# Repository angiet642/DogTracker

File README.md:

# DogTracker
__Authors: Kylee and Angie__

### Purpose 

A common issue pet-owners face is discovering that their pet has escaped the house. To prevent this situation, our team is interested in designing a low-power dog tracker using LoRa. Unlike other pet-tracking collars, our system will implement a training technique by emitting a 25KHz sound wave if the pet is found outside of a user-defined geo fence. For example, if the user would like to train their dog to avoid a specific area of the backyard, our device will detect whether the dog is in this region and emit the high frequency sound if so.

### System diagram   
The proposed design of the pet-tracker system is illustrated in the block diagram below.
<p>
  
  <p> Figure 1: System Level Block Diagram
</p>

### Proposed schedule
| Week  | Date | Tasks 
| ------------- | ------------- | ------------- |
| Week 7 | Feb 13-Feb 19  | - [x] Order parts <br />- [ ] Review PCB and Schematic with Steve and Joanna   |
| Week 8 | Feb 20-Feb 26  | - [x] Submit PCB for fabriciation | 
| Week 9 | Feb 27-March 5  | - [ ] Bring up and test boards | 
| Week 10 | March 6-March 12  | - [ ] Demo | 

### Verification
To verify our system, we will first verify the functionality of each module before methodically combining things into our final system. The steps are outlined below.

#### Before final PCB comes back: 
- [x] Upload basic Blink code to M4 Feather Board
- [x] Write basic transmit/recieve code for SX1280 using this [reference](https://github.com/maholli/CircuitPython_SX1280) (In progress)
- [ ] Hook up SX1280 to SPI port of any available micro and run transmit code while probing antenna line with Spectrum Analyzer
- [ ] Connect additional SX1280 board and have both transmit and recieve data \
#### After final PCB comes back:
- [ ] Again, verify transmit and recieve of SX1280 module on our PCB
- [ ] Connect SX1280 to ESP32 (the "base station") and try sending and recieving from our PCB
- [ ] Connect ESP32 to wifi and verify that there isn't any interference between Lora and WIFI
- [ ] Independently turn on GPS and test reading cordinates
- [ ] Turn on both SX1280 and GPS and run code to intermittently send GPS coordinates to "base station" 
- [ ] Configure pedometer to read step count on the microcontroller
- [ ] Read pedometer at the same time as reading GPS and sending Lora
- [ ] Confgure Ultrasonic piezo buzzer and try running at 25kHz, certain apps will verify sound since it's beyond the human range
- [ ] Upload code for runnng piezzo buzzer from the "base station" when dog is out of range
- [ ] Run all four modules at the same time 
- [ ] Have "base station"  upload information to a website hosted on the the Things network

### Demo Plan
Our demo will be putting the collar on a fellow classmate and having them run around the engineering quad to show the real time updates in GPS coordinates on the base station, which will be set up in the lab. Finally, we will show that when our classmate goes out of the user-defined range, the piezzo buzzer will turn on which can be verified with [this app](https://play.google.com/store/apps/details?id=com.microcadsystems.serge.ultrasounddetector&hl=en_US&gl=US)

### In our write up, we will discuss the following
- importance and novelty of the idea 
- description of chosen features 
- high level system discussion
- schematic walkthrough 
- examination of different protocols SPI/I2C/UART 
- Review of RF components eg LoRa, WiFi 
- analysis of challenges or drawbacks
- improvements going forward 
- concluding remarks on our project 

### Challenges
The most difficult steps is getting the PCB right the first time around. We have been meticulously researching parts and going through datasheets to make sure we understand everything that we need for our final PCB. We also plan to have Joanna, Greig, and Steve verify the schematic before we submit it to JLCPCB. 

We have already gotten our parts list checked off and ordered. After submitting our final PCB, we will begin working on the software side of our project. There is a sufficient amount of code to write but none will be outside of our domain given that there's a lot of GPS/LORA/SPI/I2C libraries in Circuit python. 

### Project Links:
Bill of Materials can be found [here](https://github.com/krsandwich/DogTracker/tree/master/Hardware/BOM) \
KICAD Project can be found [here](https://github.com/krsandwich/DogTracker/tree/master/Hardware/Kicad)\
M4 Feather Express Schematic can be found [here](https://learn.adafruit.com/assets/57242)

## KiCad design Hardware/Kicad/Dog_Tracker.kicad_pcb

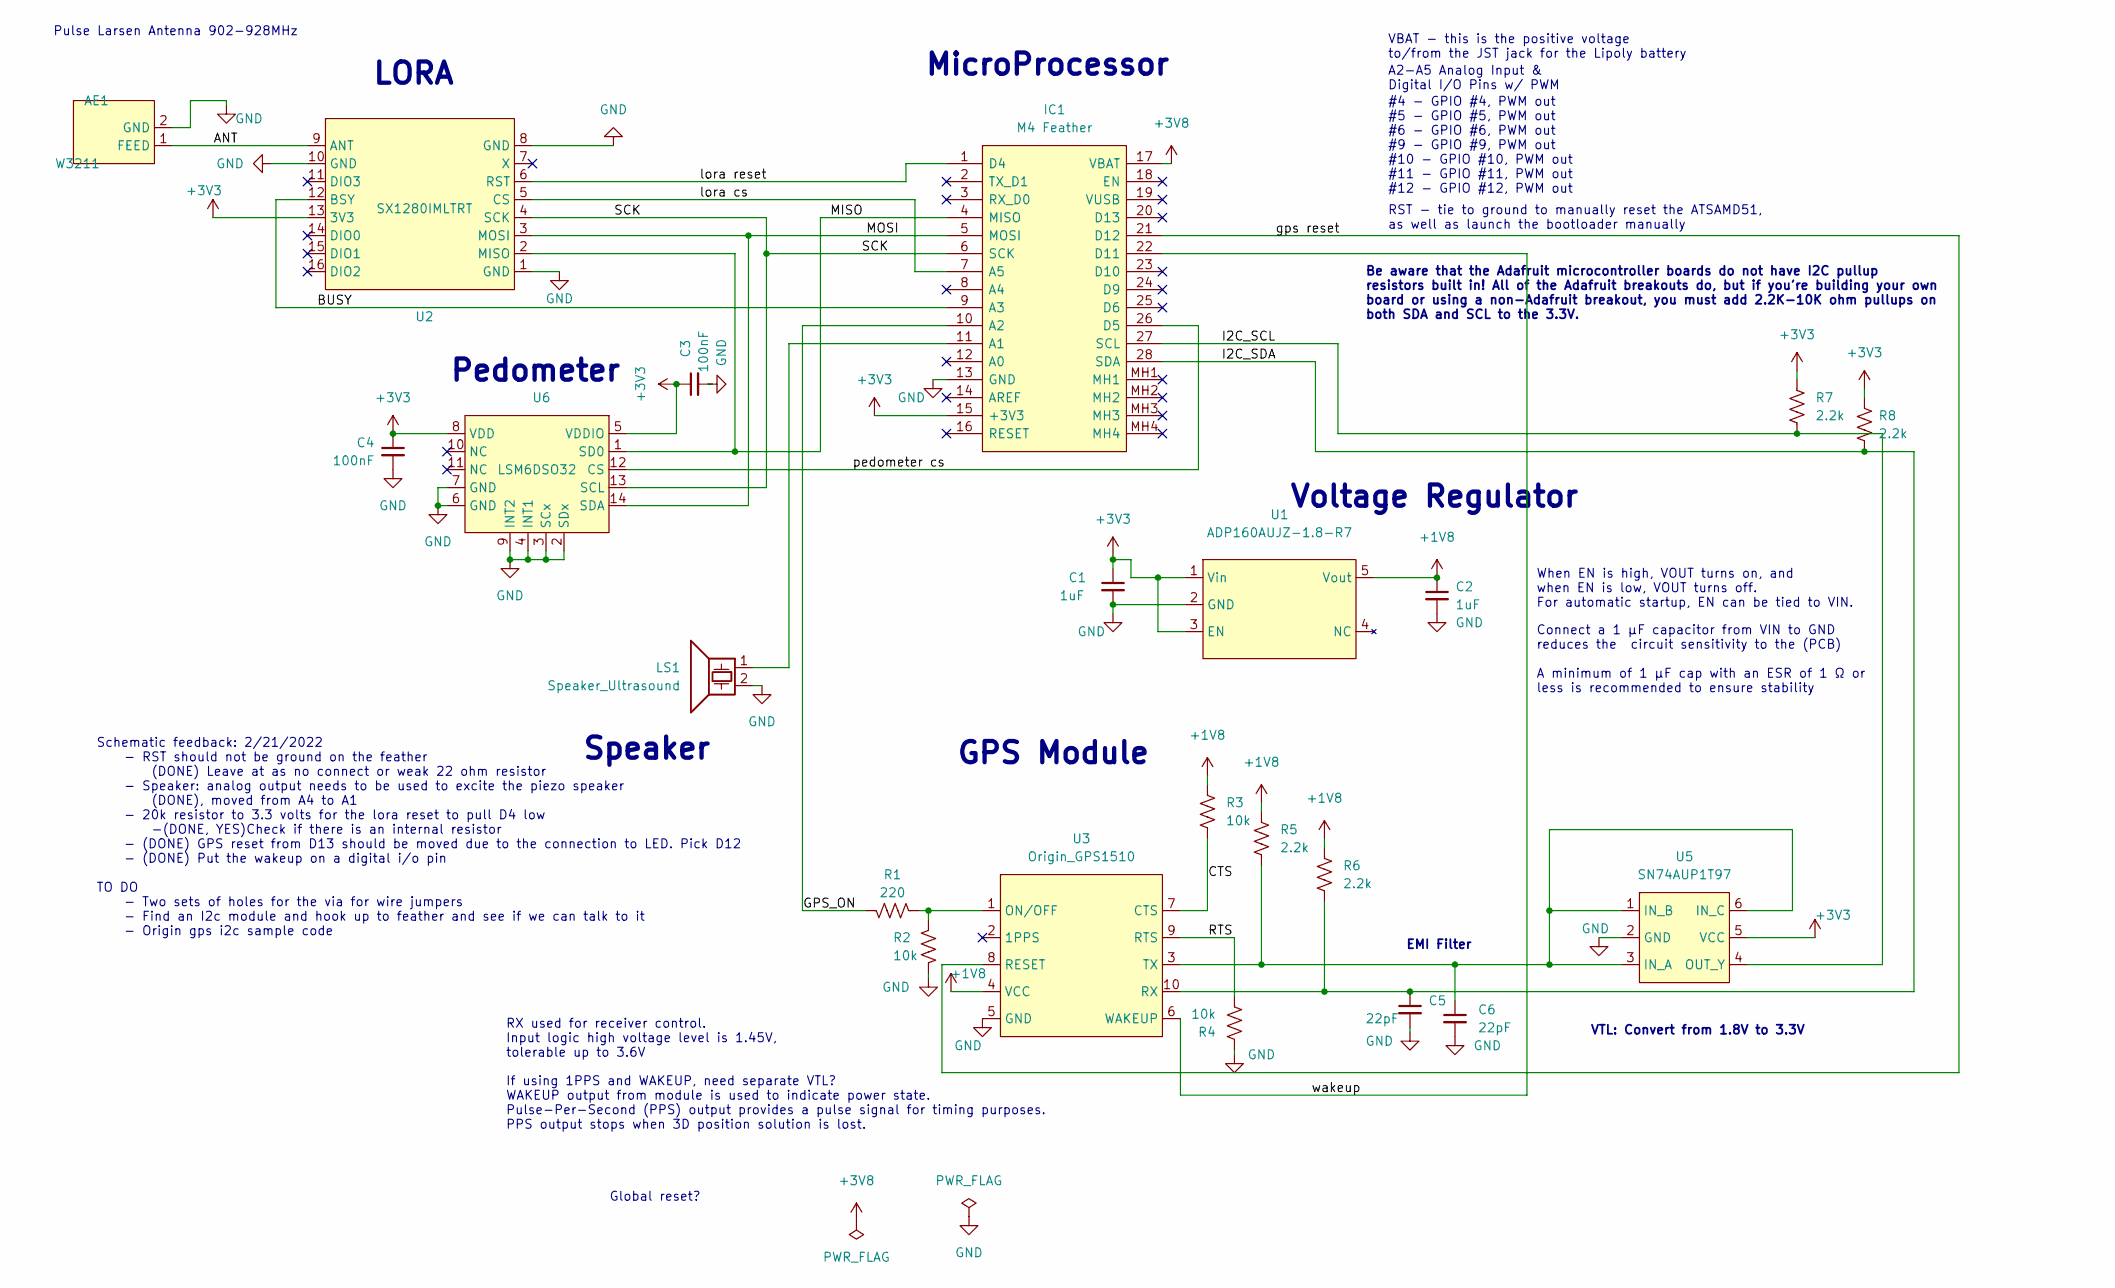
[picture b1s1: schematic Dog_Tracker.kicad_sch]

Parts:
AE1: W3211
C1, C2: 1uF; C_0402_1005Metric
C3, C4: 100nF; C_0402_1005Metric
C5, C6: 22pF; C_0402_1005Metric
IC1: M4 Feather; Feather_M4; Manufacturer_Part_Number 3857; Mouser Part Number 485-3857
LS1: Speaker_Ultrasound; W-03A
R1: 220; R_0402_1005Metric
R2, R3, R4: 10k; R_0402_1005Metric
R5, R6, R7, R8: 2.2k; R_0402_1005Metric
U1: ADP160AUJZ-1.8-R7; SOT95P280X100
U2: SX1280IMLTRT; SX1280_Breakout
U3: Origin_GPS1510; ORG1510
U5: SN74AUP1T97; SN74AUP1T97DSFR
U6: LSM6DSO32; LSM6DSRTR

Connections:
+1V8: C2.1, R3.2, R5.2, R6.2, U1.5 (Vout), U3.4 (VCC)
+3V3: C1.1, C3.1, C4.1, IC1.15 (+3V3), R7.2, R8.2, U1.1 (Vin), U1.3 (EN), U2.13 (3V3), U5.5 (VCC), U6.5 (VDDIO), U6.8 (VDD)
+3V8: IC1.17 (VBAT)
/ANT: AE1.1 (FEED), U2.9 (ANT)
/BUSY: IC1.9 (A3), U2.12 (BSY)
/CTS: R3.1, U3.7 (CTS)
/GPS_ON: IC1.10 (A2), R1.1
/I2C_SCL: IC1.27 (SCL), R7.1, U5.4 (OUT_Y)
/I2C_SDA: C5.1, IC1.28 (SDA), R6.1, R8.1, U3.10 (RX)
/MISO: IC1.4 (MISO), U2.2 (MISO), U6.1 (SD0)
/MOSI: IC1.5 (MOSI), U2.3 (MOSI), U6.14 (SDA)
/RTS: R4.1, U3.9 (RTS)
/SCK: IC1.6 (SCK), U2.4 (SCK), U6.13 (SCL)
/gps reset: IC1.21 (D12), U3.8 (RESET)
/lora cs: IC1.7 (A5), U2.5 (CS)
/lora reset: IC1.1 (D4), U2.6 (RST)
/pedometer cs: IC1.26 (D5), U6.12 (CS)
/wakeup: IC1.22 (D11), U3.6 (WAKEUP)
GND: AE1.2 (GND), C1.2, C2.2, C3.2, C4.2, C5.2, C6.2, IC1.13 (GND), LS1.2, R2.2, R4.2, U1.2 (GND), U2.1 (GND), U2.8 (GND), U2.10 (GND), U3.5 (GND), U5.2 (GND), U6.2 (SDx), U6.3 (SCx), U6.4 (INT1), U6.6 (GND), U6.7 (GND), U6.9 (INT2)
unnamed: C6.1, R5.1, U3.3 (TX), U5.1 (IN_B), U5.3 (IN_A), U5.6 (IN_C)
unnamed: IC1.11 (A1), LS1.1
unnamed: R1.2, R2.1, U3.1 (ON/OFF)

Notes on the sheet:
#4 - GPIO #4, PWM out #5 - GPIO #5, PWM out #6 - GPIO #6, PWM out #9 - GPIO #9, PWM out #10 - GPIO #10, PWM out #11 - GPIO #11, PWM out #12 - GPIO #12, PWM out
VTL: Convert from 1.8V to 3.3V
Pulse Larsen Antenna 902-928MHz
Voltage Regulator
EMI Filter
LORA
Pedometer
VBAT - this is the positive voltage to/from the JST jack for the Lipoly battery
MicroProcessor
RX used for receiver control. Input logic high voltage level is 1.45V, tolerable up to 3.6V
If using 1PPS and WAKEUP, need separate VTL? WAKEUP output from module is used to indicate power state. Pulse-Per-Second (PPS) output provides a pulse signal for timing purposes. PPS output stops when 3D position solution is lost.
When EN is high, VOUT turns on, and when EN is low, VOUT turns off. For automatic startup, EN can be tied to VIN.
A2-A5 Analog Input & Digital I/O Pins w/ PWM
Global reset?
Connect a 1 μF capacitor from VIN to GND reduces the circuit sensitivity to the (PCB) A minimum of 1 μF cap with an ESR of 1 Ω or less is recommended to ensure stability
GPS Module
Schematic feedback: 2/21/2022 - RST should not be ground on the feather (DONE) Leave at as no connect or weak 22 ohm resistor - Speaker: analog output needs to be used to excite the piezo speaker (DONE), moved from A4 to A1 - 20k resistor to 3.3 volts for the lora reset to pull D4 low -(DONE, YES)C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
Be aware that the Adafruit microcontroller boards do not have I2C pullup resistors built in! All of the Adafruit breakouts do, but if you're building your own board or using a non-Adafruit breakout, you must add 2.2K-10K ohm pullups on both SDA and SCL to the 3.3V.
RST - tie to ground to manually reset the ATSAMD51, as well as launch the bootloader manually
Speaker

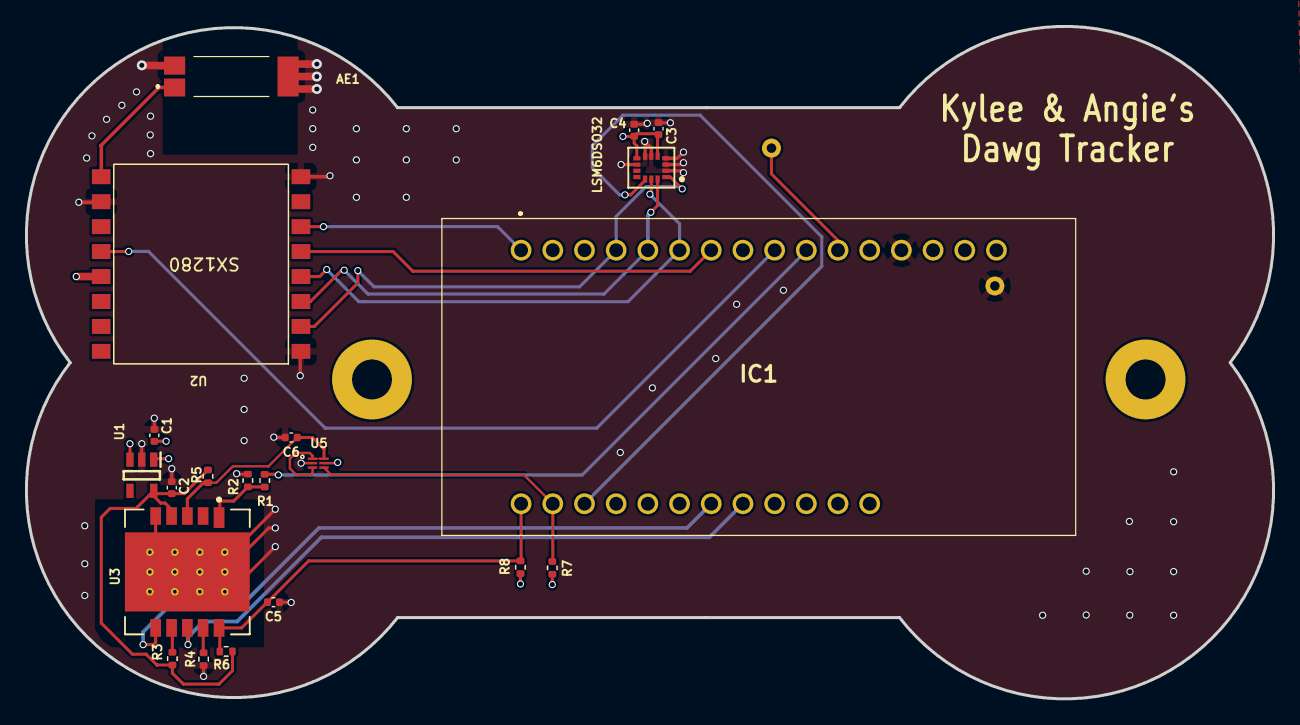
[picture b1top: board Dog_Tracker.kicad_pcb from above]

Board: 4 copper layers, 100.0 x 53.9 mm, 22 parts (1 on the bottom side), 21 nets.

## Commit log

2022-02-11 update symbols
2022-02-12 'updated feather'
2022-02-13 add text, hope this works
2022-02-13 'rearrange schematic'
2022-02-14 BOM info
2022-02-14 change readme name
2022-02-14 update bom
2022-02-14 change folder name
2022-02-14 folder name changed
2022-02-14 feather pinout document added
2022-02-14 update schematic
2022-02-14 update reset
2022-02-14 fixed pedometer
2022-02-14 'assigned footprints'
2022-02-14 update last footprint
2022-02-15 fixed typo
2022-02-15 'wire the schematic'
2022-02-15 'wire i2c'
2022-02-15 schematic fixed
2022-02-16 saved
2022-02-16 add block diagram
2022-02-16 'fixed erc, need to fix warnings'
2022-02-16 no errors, no warnings
2022-02-21 footprint speaker
2022-02-22 removed footprints and added the origin gps only. updated schematic per steves feedback
2022-02-22 added footprints
2022-02-22 'update 3214 to 3211'
2022-02-22 'pcb floor plan initiated'
2022-02-22 fixed all footprint and added SX1280
2022-02-23 'remove emi filter and use caps'
2022-02-24 pcb check
2022-02-24 layout done
2022-02-24 gerbers
2022-02-26 'update pcb based on steves comments'
2022-02-26 fixed footprint
2022-02-26 'add vias'
2022-02-26 'update schematic pdf'
2022-02-28 added esp32 code
2022-02-28 Create GPS_HardwareSerial_Parsing
2022-03-04 'sent for fab'
2022-03-18 added final report
